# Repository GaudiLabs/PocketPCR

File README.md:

# PocketPCR
Pocket size USB powered PCR Thermo Cycler.

For more information see project website:
http://gaudi.ch/PocketPCR/

Designed by GaudiLabs:
http://www.gaudi.ch/GaudiLabs/

Support the development of Open Science Hardware:
https://gaudishop.ch/

### License

PocketPCR, all design files and software are licensed under a GNU GENERAL PUBLIC LICENSE
See license file in the repository.

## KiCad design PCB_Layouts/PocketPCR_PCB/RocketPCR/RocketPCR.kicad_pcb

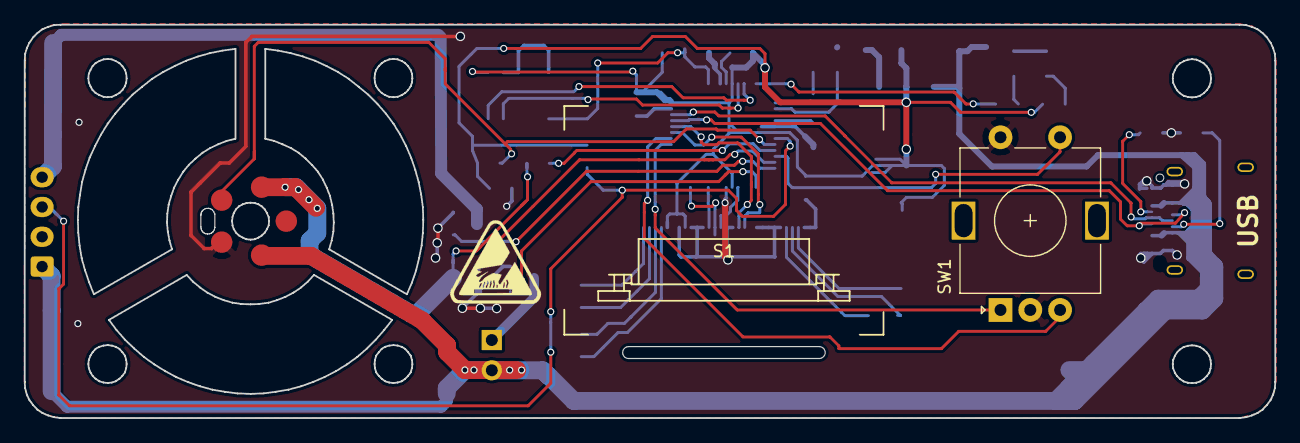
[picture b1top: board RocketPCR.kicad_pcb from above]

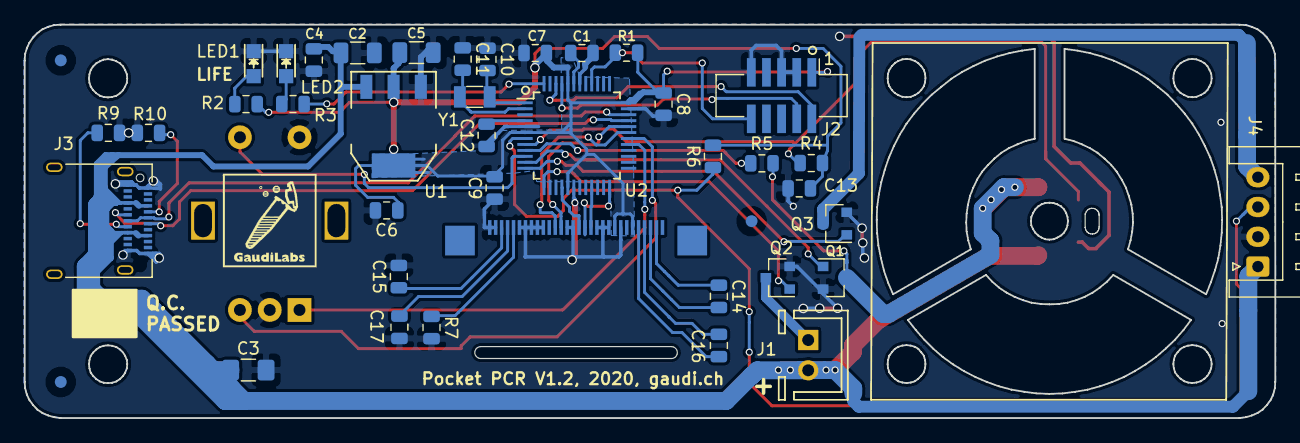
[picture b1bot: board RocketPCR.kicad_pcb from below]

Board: 2 copper layers, 105.0 x 33.0 mm, 48 parts (41 on the bottom side), 41 nets.

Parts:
C1, C4, C12, C14, C16: 1uF; C_0805_2012Metric
C2: 100uF,35V; C_1206_3216Metric
C3: 22uF; C_1206_3216Metric_Pad1.42x1.75mm_HandSolder
C5: 22uF; C_1206_3216Metric
C6, C7, C8, C9, C13: 100nF; C_0805_2012Metric
C10, C11: 22pF; C_0805_2012Metric
C15, C17: 2.2uF; C_0805_2012Metric
J1: Conn_01x02_Male; PinHeader_JST_1x02_P2.54mm_Vertical
J2: Conn_02x05_Odd_Even; Pin_Header_Straight_2x05_Pitch1.27mm_SMD
J3: USB_C_Receptacle; USB_C_Receptacle_Amphenol_12401610E4-2A
J4: Conn_01x04_Female; JST_XH_S04B-XH-A_1x04_P2.50mm_Horizontal
LED1, LED2: LED; LED-0805
Q1, Q2, Q3: Q_NMOS_GSD; SOT-23
R1: 10k; R_0805_2012Metric
R2, R3: 390; R_0805_2012Metric
R4, R6: 4.7k; R_0805_2012Metric
R5, R7: 390k; R_0805_2012Metric
R9, R10: 5k; R_0805_2012Metric
S1: OLED_DISPLAY; OLED_096_1_Flip
SW1: Rotary_Encoder_Switch; RotaryEncoder_Alps_EC11E-Switch_Vertical_H20mm
U1: TLV1117-33; SOT-223
U2: SAMD21G18B-A changed from SAML21; TQFP-48_7x7mm_Pitch0.5mm
X2, X3, X4, X6, X7: PAD; SolderPad1_8mm
X9, X10, X11: PAD; Fiducial_1mm_Dia_2.54mm_Outer_CopperBottom
Y1: 32.765; Crystal_SMD_3215-2pin_3.2x1.5mm

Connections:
+3V3: C5.1, C6.1, C7.1, C8.1, C9.2, C13.2, J2.1, R1.2, R2.1, R4.2, R6.2, S1.6, S1.9, U1.2, U2.6, U2.17, U2.36, U2.44
AREF: C12.2, U2.4
BLOCK: Q1.1, U2.11
D+: J3.A6, J3.B6, U2.34
D-: J3.A7, J3.B7, U2.33
DISP_CS: S1.13, U2.21
DISP_DC: S1.15, U2.16
DISP_RES: S1.14, U2.24
DISP_SCL: S1.18, U2.32
DISP_SDA: S1.19, U2.31
ENC1: SW1.A, U2.29
ENC2: SW1.B, U2.30
FAN: Q2.1, U2.13
GND: C1.2, C2.2, C3.2, C4.1, C5.2, C6.2, C7.2, C8.2, C9.1, C10.1, C11.1, C12.1, C13.1, C15.2, C17.2, J2.3, J2.5, J2.9, J3.A1, J3.A12, J3.B1, J3.B12, J4.2, LED1.1, LED2.1, Q1.2, Q2.2, Q3.2, R7.2, R9.2, R10.2, S1.8, S1.10, S1.11, S1.12, S1.16, S1.17, S1.21, S1.22, S1.23, S1.24, S1.25, S1.29, S1.30, SW1.C, SW1.S2, U1.1, U2.5, U2.18, U2.35, U2.42, X6.1
LID: Q3.1, U2.12
unnamed: C1.1, U2.43
unnamed: C10.2, U2.1, Y1.1
unnamed: C11.2, U2.2, Y1.2
unnamed: C14.1, S1.2
unnamed: C14.2, S1.3
unnamed: C15.1, S1.28
unnamed: C16.1, S1.4
unnamed: C16.2, S1.5
unnamed: C17.1, S1.27
unnamed: J1.1, Q2.3
unnamed: J3.A5, R10.1
unnamed: J3.B5, R9.1
unnamed: J4.4, Q3.3
unnamed: LED1.2, R2.2
unnamed: LED2.2, R3.2
unnamed: R5.1, U2.9
unnamed: R7.1, S1.26
RESET: J2.10, R1.1, U2.40
RX_LED: R3.1, U2.48
SW1: SW1.S1, U2.10
SWCLK: J2.4, U2.45
SWDIO: J2.2, U2.46
TEMP_BLOCK: R4.1, U2.8, X3.1
TEMP_LID: J4.3, R6.1, U2.7
VSENS: Q1.3, R5.2, X2.1
V_USB: C2.1, C3.1, C4.2, J1.2, J3.A4, J3.A9, J3.B4, J3.B9, J4.1, U1.3, X4.1

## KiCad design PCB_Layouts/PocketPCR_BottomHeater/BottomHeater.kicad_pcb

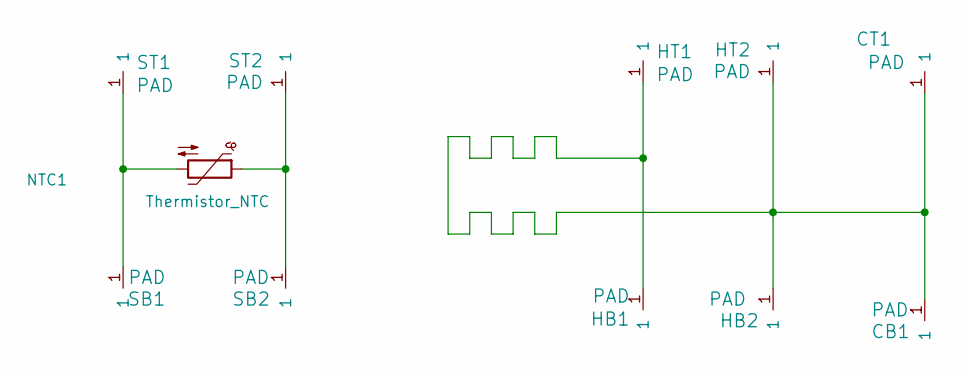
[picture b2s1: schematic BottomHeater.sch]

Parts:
CB1: PAD; SolderPad1_8mm
CT1: PAD; SolderPad1_8mm
HB1, HB2: PAD; SolderPad1_8mm
HT1, HT2: PAD; SolderPad1_8mm
NTC1: Thermistor_NTC; C_0402_1005Metric
SB1, SB2: PAD; SolderPad1_8mm
ST1, ST2: PAD; SolderPad1_8mm

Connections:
unnamed: CB1.1, CT1.1, HB1.1, HB2.1, HT1.1, HT2.1
unnamed: NTC1.1, SB2.1, ST2.1
unnamed: NTC1.2, SB1.1, ST1.1

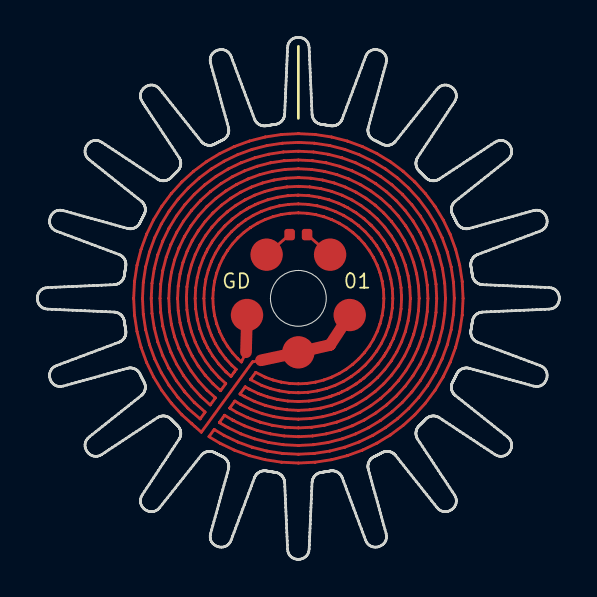
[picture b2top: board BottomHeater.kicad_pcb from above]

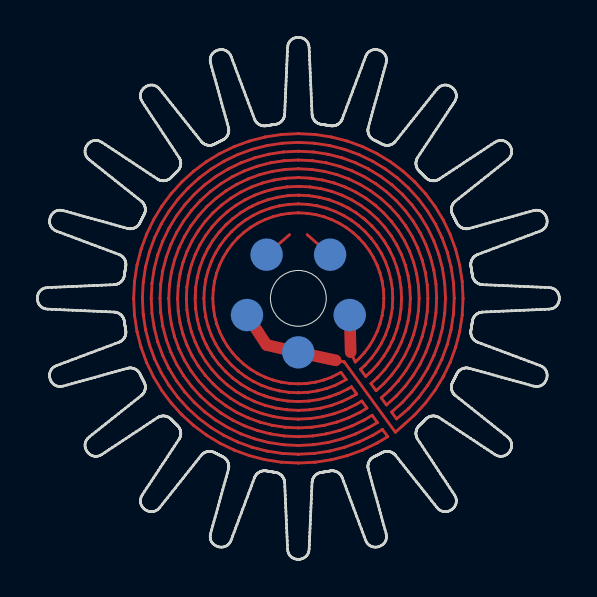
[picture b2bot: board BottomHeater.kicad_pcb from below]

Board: 2 copper layers, 29.0 x 29.0 mm, 11 parts (5 on the bottom side), 3 nets.

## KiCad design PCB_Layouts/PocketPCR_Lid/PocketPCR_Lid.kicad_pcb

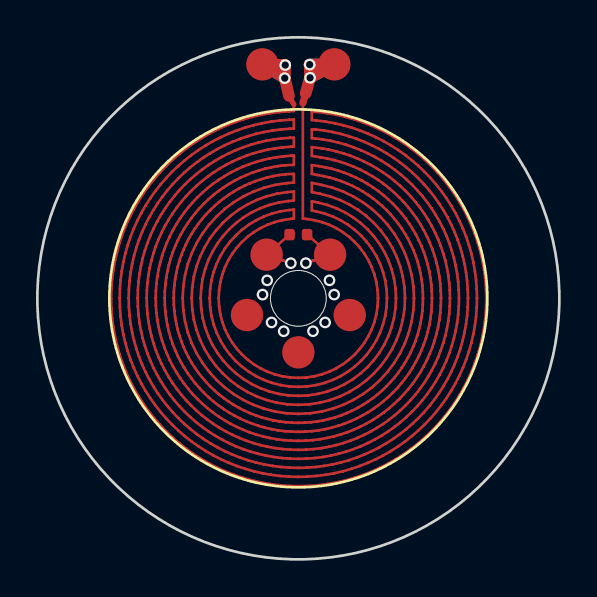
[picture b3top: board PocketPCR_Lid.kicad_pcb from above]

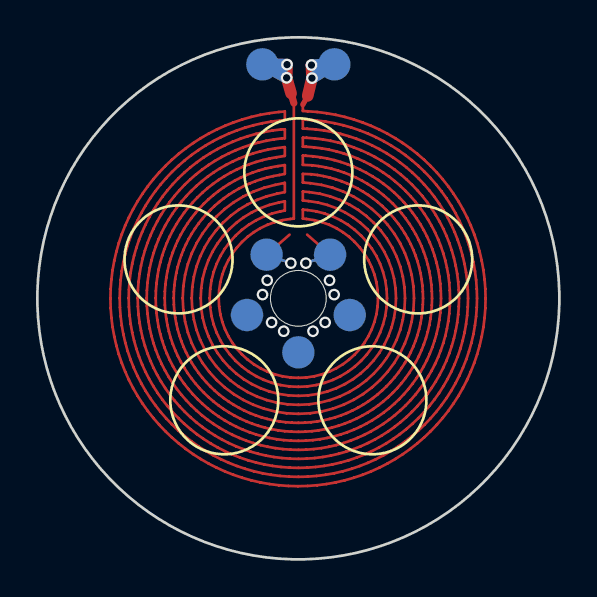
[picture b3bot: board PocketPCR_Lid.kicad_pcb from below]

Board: 2 copper layers, 29.0 x 29.0 mm, 15 parts (7 on the bottom side), 4 nets.

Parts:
CB1: PAD; SolderPad1_8mm
CT1: PAD; SolderPad1_8mm
HB1, HB2: PAD; SolderPad1_8mm
HT1, HT2: PAD; SolderPad1_8mm
NTC1: Thermistor_NTC; C_0402_1005Metric
SB1, SB2, SB2#2, SB2#3, SB2#4, SB2#5: PAD; SolderPad1_8mm
ST1, ST2: PAD; SolderPad1_8mm

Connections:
unnamed: CB1.1, CT1.1
unnamed: HB1.1, HB2.1, HT1.1, HT2.1
unnamed: NTC1.1, SB2#5.1, ST2.1
unnamed: NTC1.2, SB1.1, ST1.1

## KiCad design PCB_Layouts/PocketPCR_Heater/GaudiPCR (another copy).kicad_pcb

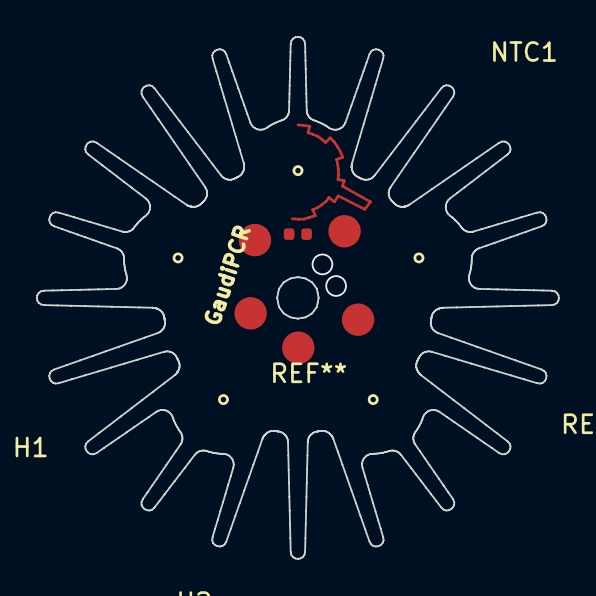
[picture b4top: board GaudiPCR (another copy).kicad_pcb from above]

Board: 2 copper layers, 29.0 x 29.0 mm, 5 parts (0 on the bottom side), 3 nets.

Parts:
H1, H2: PAD; SolderPad1_8mm
NTC1: Thermistor_NTC; C_0402_1005Metric
TH1, TH2: PAD; SolderPad1_8mm

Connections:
/HEATER: H1.1, H2.1
unnamed: NTC1.1, TH1.1
unnamed: NTC1.2, TH2.1

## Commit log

2019-08-28 First upload PocketPCR is open source
2019-09-22 Storing settings in Flashmemory there is no eeprom...
2019-12-06 New Version with Bottom Heater Improved software
2020-03-18 Updated PCB, BOM, added Heater Hardware
2020-04-08 Production Release ReadMe
2020-11-17 Updated Version code
2020-11-18 Adapted code to newest Display Library just one line
